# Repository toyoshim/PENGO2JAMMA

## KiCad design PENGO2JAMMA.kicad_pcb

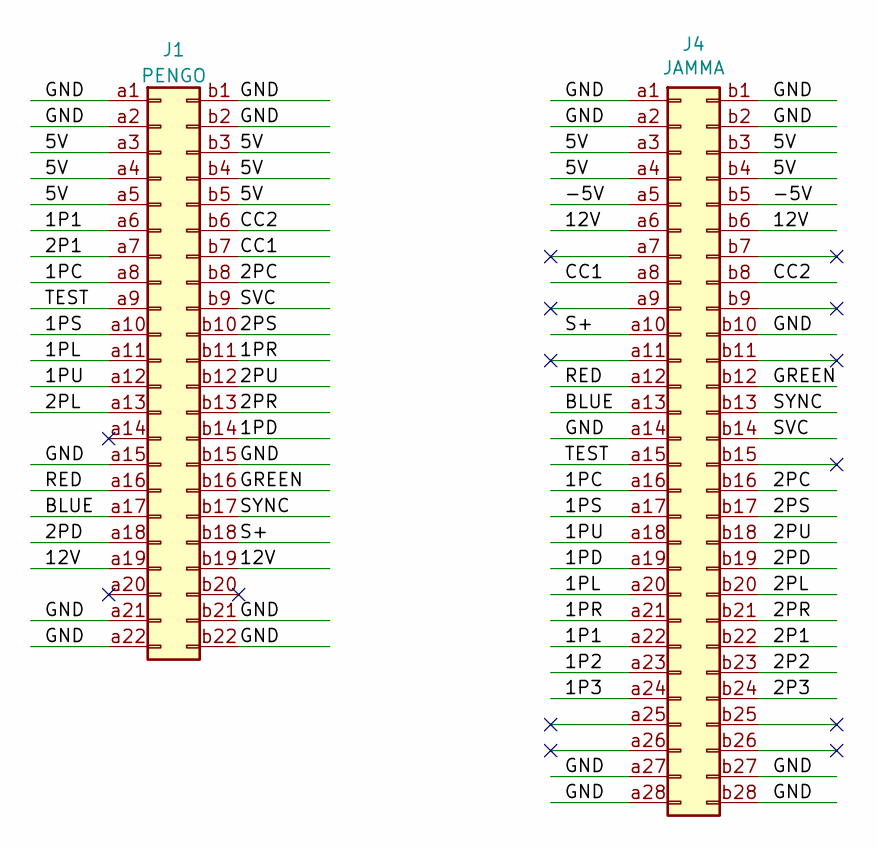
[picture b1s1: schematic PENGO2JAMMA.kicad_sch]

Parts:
J1: PENGO; Connector_Edge_3.96mm_02x22_Row_PENGO
J4: JAMMA; Connector_Edge_3.96mm_02x28_Row_JAMMA

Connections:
/1P1: J1.a6, J4.a22
/1P2: J4.a23
/1P3: J4.a24
/1PC: J1.a8, J4.a16
/1PD: J1.b14, J4.a19
/1PL: J1.a11, J4.a20
/1PR: J1.b11, J4.a21
/1PS: J1.a10, J4.a17
/1PU: J1.a12, J4.a18
/2P1: J1.a7, J4.b22
/2P2: J4.b23
/2P3: J4.b24
/2PC: J1.b8, J4.b16
/2PD: J1.a18, J4.b19
/2PL: J1.a13, J4.b20
/2PR: J1.b13, J4.b21
/2PS: J1.b10, J4.b17
/2PU: J1.b12, J4.b18
/5V: J1.a3, J1.a4, J1.a5, J1.b3, J1.b4, J1.b5, J4.a3, J4.a4, J4.b3, J4.b4
/12V: J1.a19, J1.b19, J4.a6, J4.b6
/-5V: J4.a5, J4.b5
/BLUE: J1.a17, J4.a13
/CC1: J1.b7, J4.a8
/CC2: J1.b6, J4.b8
/GND: J1.a1, J1.a2, J1.a15, J1.a21, J1.a22, J1.b1, J1.b2, J1.b15, J1.b21, J1.b22, J4.a1, J4.a2, J4.a14, J4.a27, J4.a28, J4.b1, J4.b2, J4.b10, J4.b27, J4.b28
/GREEN: J1.b16, J4.b12
/RED: J1.a16, J4.a12
/S+: J1.b18, J4.a10
/SVC: J1.b9, J4.b14
/SYNC: J1.b17, J4.b13
/TEST: J1.a9, J4.a15

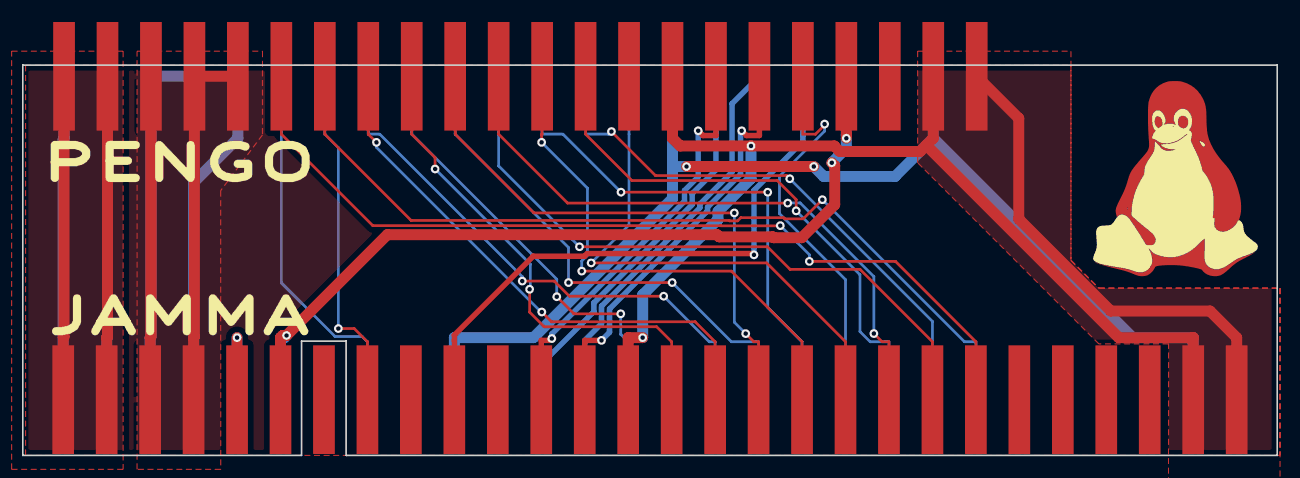
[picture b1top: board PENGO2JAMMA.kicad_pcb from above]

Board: 2 copper layers, 114.3 x 35.6 mm, 4 parts (0 on the bottom side), 27 nets.

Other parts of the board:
G1: LOGO; Penguin
G2: LOGO; Penguin_mask
